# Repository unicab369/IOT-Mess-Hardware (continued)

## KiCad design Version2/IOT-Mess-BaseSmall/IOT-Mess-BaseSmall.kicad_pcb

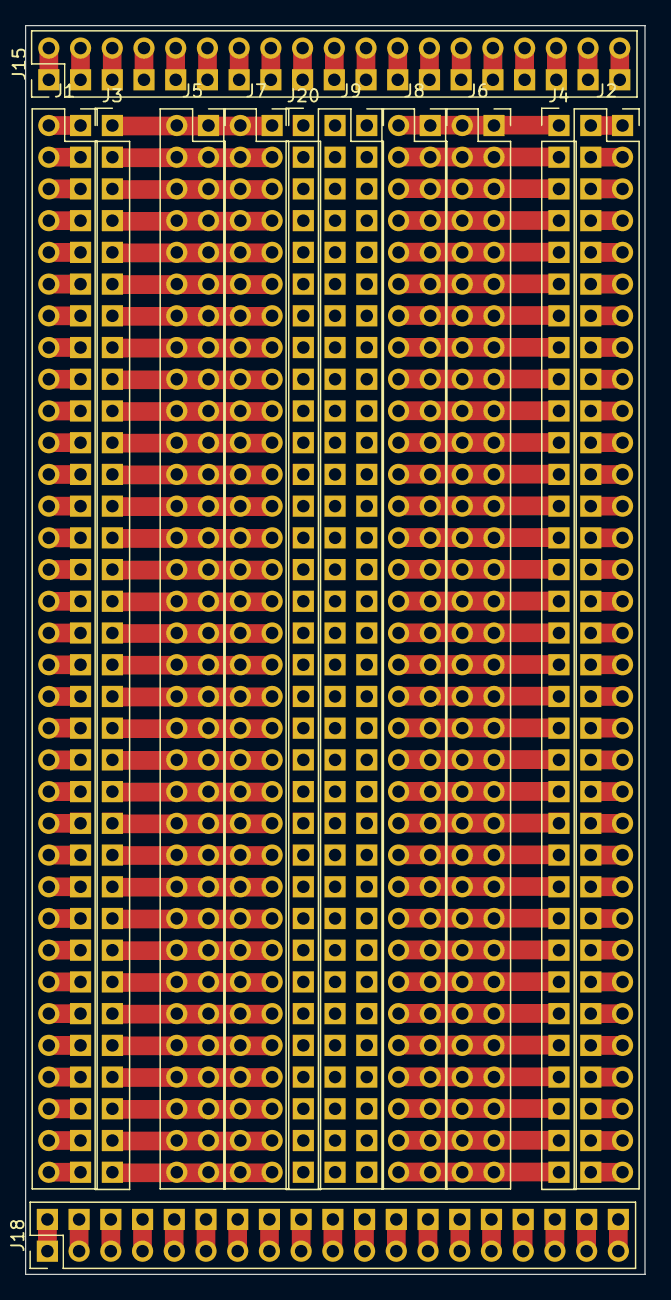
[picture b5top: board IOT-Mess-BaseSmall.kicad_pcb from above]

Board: 2 copper layers, 49.6 x 100.0 mm, 12 parts (0 on the bottom side), 174 nets.

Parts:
J1, J2, J5, J6, J7, J8, J9: Conn_02x34_Odd_Even; PinSocket_2x34_P2.54mm_Vertical
J3, J4, J20: Conn_01x34_Pin; PinHeader_1x34_P2.54mm_Vertical
J15, J18: Conn_02x19_Odd_Even; PinHeader_2x19_P2.54mm_Vertical

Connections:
/A1: J1.1, J1.2
/A2: J1.3, J1.4
/A3: J1.5, J1.6
/A4: J1.7, J1.8
/A5: J1.9, J1.10
/A6: J1.11, J1.12
/A7: J1.13, J1.14
/A8: J1.15, J1.16
/A9: J1.17, J1.18
/A10: J1.19, J1.20
/A11: J1.21, J1.22
/A12: J1.23, J1.24
/A13: J1.25, J1.26
/A14: J1.27, J1.28
/A15: J1.29, J1.30
/A16: J1.31, J1.32
/A17: J1.33, J1.34
/A18: J1.35, J1.36
/A19: J1.37, J1.38
/A20: J1.39, J1.40
/A21: J1.41, J1.42
/A22: J1.43, J1.44
/A23: J1.45, J1.46
/A24: J1.47, J1.48
/A25: J1.49, J1.50
/A26: J1.51, J1.52
/A27: J1.53, J1.54
/A28: J1.55, J1.56
/A29: J1.57, J1.58
/A30: J1.59, J1.60
/A31: J1.61, J1.62
/A32: J1.63, J1.64
/A33: J1.65, J1.66
/A34: J1.67, J1.68
/B1: J3.1, J5.1, J5.2, J7.1, J7.2
/B2: J3.2, J5.3, J5.4, J7.3, J7.4
/B3: J3.3, J5.5, J5.6, J7.5, J7.6
/B4: J3.4, J5.7, J5.8, J7.7, J7.8
/B5: J3.5, J5.9, J5.10, J7.9, J7.10
/B6: J3.6, J5.11, J5.12, J7.11, J7.12
/B7: J3.7, J5.13, J5.14, J7.13, J7.14
/B8: J3.8, J5.15, J5.16, J7.15, J7.16
/B9: J3.9, J5.17, J5.18, J7.17, J7.18
/B10: J3.10, J5.19, J5.20, J7.19, J7.20
/B11: J3.11, J5.21, J5.22, J7.21, J7.22
/B12: J3.12, J5.23, J5.24, J7.23, J7.24
/B13: J3.13, J5.25, J5.26, J7.25, J7.26
/B14: J3.14, J5.27, J5.28, J7.27, J7.28
/B15: J3.15, J5.29, J5.30, J7.29, J7.30
/B16: J3.16, J5.31, J5.32, J7.31, J7.32
/B17: J3.17, J5.33, J5.34, J7.33, J7.34
/B18: J3.18, J5.35, J5.36, J7.35, J7.36
/B19: J3.19, J5.37, J5.38, J7.37, J7.38
/B20: J3.20, J5.39, J5.40, J7.39, J7.40
/B21: J3.21, J5.41, J5.42, J7.41, J7.42
/B22: J3.22, J5.43, J5.44, J7.43, J7.44
/B23: J3.23, J5.45, J5.46, J7.45, J7.46
/B24: J3.24, J5.47, J5.48, J7.47, J7.48
/B25: J3.25, J5.49, J5.50, J7.49, J7.50
/B26: J3.26, J5.51, J5.52, J7.51, J7.52
/B27: J3.27, J5.53, J5.54, J7.53, J7.54
/B28: J3.28, J5.55, J5.56, J7.55, J7.56
/B29: J3.29, J5.57, J5.58, J7.57, J7.58
/B30: J3.30, J5.59, J5.60, J7.59, J7.60
/B31: J3.31, J5.61, J5.62, J7.61, J7.62
/B32: J3.32, J5.63, J5.64, J7.63, J7.64
/B33: J3.33, J5.65, J5.66, J7.65, J7.66
/B34: J3.34, J5.67, J5.68, J7.67, J7.68
/C1: J2.1, J2.2
/C2: J2.3, J2.4
/C3: J2.5, J2.6
/C4: J2.7, J2.8
/C5: J2.9, J2.10
/C6: J2.11, J2.12
/C7: J2.13, J2.14
/C8: J2.15, J2.16
/C9: J2.17, J2.18
/C10: J2.19, J2.20
/C11: J2.21, J2.22
/C12: J2.23, J2.24
/C13: J2.25, J2.26
/C14: J2.27, J2.28
/C15: J2.29, J2.30
/C16: J2.31, J2.32
/C17: J2.33, J2.34
/C18: J2.35, J2.36
/C19: J2.37, J2.38
/C20: J2.39, J2.40
/C21: J2.41, J2.42
/C22: J2.43, J2.44
/C23: J2.45, J2.46
/C24: J2.47, J2.48
/C25: J2.49, J2.50
/C26: J2.51, J2.52
/C27: J2.53, J2.54
/C28: J2.55, J2.56
/C29: J2.57, J2.58
/C30: J2.59, J2.60
/C31: J2.61, J2.62
/C32: J2.63, J2.64
/C33: J2.65, J2.66
/C34: J2.67, J2.68
/D1: J4.1, J6.1, J6.2, J8.1, J8.2
/D2: J4.2, J6.3, J6.4, J8.3, J8.4
/D3: J4.3, J6.5, J6.6, J8.5, J8.6
/D4: J4.4, J6.7, J6.8, J8.7, J8.8
/D5: J4.5, J6.9, J6.10, J8.9, J8.10
/D6: J4.6, J6.11, J6.12, J8.11, J8.12
/D7: J4.7, J6.13, J6.14, J8.13, J8.14
/D8: J4.8, J6.15, J6.16, J8.15, J8.16
/D9: J4.9, J6.17, J6.18, J8.17, J8.18
/D10: J4.10, J6.19, J6.20, J8.19, J8.20
/D11: J4.11, J6.21, J6.22, J8.21, J8.22
/D12: J4.12, J6.23, J6.24, J8.23, J8.24
/D13: J4.13, J6.25, J6.26, J8.25, J8.26
/D14: J4.14, J6.27, J6.28, J8.27, J8.28
/D15: J4.15, J6.29, J6.30, J8.29, J8.30
/D16: J4.16, J6.31, J6.32, J8.31, J8.32
/D17: J4.17, J6.33, J6.34, J8.33, J8.34
/D18: J4.18, J6.35, J6.36, J8.35, J8.36
/D19: J4.19, J6.37, J6.38, J8.37, J8.38
/D20: J4.20, J6.39, J6.40, J8.39, J8.40
/D21: J4.21, J6.41, J6.42, J8.41, J8.42
/D22: J4.22, J6.43, J6.44, J8.43, J8.44
/D23: J4.23, J6.45, J6.46, J8.45, J8.46
/D24: J4.24, J6.47, J6.48, J8.47, J8.48
/D25: J4.25, J6.49, J6.50, J8.49, J8.50
/D26: J4.26, J6.51, J6.52, J8.51, J8.52
/D27: J4.27, J6.53, J6.54, J8.53, J8.54
/D28: J4.28, J6.55, J6.56, J8.55, J8.56
/D29: J4.29, J6.57, J6.58, J8.57, J8.58
/D30: J4.30, J6.59, J6.60, J8.59, J8.60
/D31: J4.31, J6.61, J6.62, J8.61, J8.62
/D32: J4.32, J6.63, J6.64, J8.63, J8.64
/D33: J4.33, J6.65, J6.66, J8.65, J8.66
/D34: J4.34, J6.67, J6.68, J8.67, J8.68
/E1: J15.1, J15.2
/E2: J15.3, J15.4
/E3: J15.5, J15.6
/E4: J15.7, J15.8
/E5: J15.9, J15.10
/E6: J15.11, J15.12
/E7: J15.13, J15.14
/E8: J15.15, J15.16
/E9: J15.17, J15.18
/E10: J15.19, J15.20
/E11: J15.21, J15.22
/E12: J15.23, J15.24
/E13: J15.25, J15.26
/E14: J15.27, J15.28
/E15: J15.29, J15.30
/E16: J15.31, J15.32
/E17: J15.33, J15.34
/E18: J15.35, J15.36
/E19: J15.37, J15.38
/F1: J18.1, J18.2
/F2: J18.3, J18.4
/F3: J18.5, J18.6
/F4: J18.7, J18.8
/F5: J18.9, J18.10
/F6: J18.11, J18.12
/F7: J18.13, J18.14
/F8: J18.15, J18.16
/F9: J18.17, J18.18
/F10: J18.19, J18.20
/F11: J18.21, J18.22
/F12: J18.23, J18.24
/F13: J18.25, J18.26
/F14: J18.27, J18.28
/F15: J18.29, J18.30
/F16: J18.31, J18.32
/F17: J18.33, J18.34
/F18: J18.35, J18.36
/F19: J18.37, J18.38

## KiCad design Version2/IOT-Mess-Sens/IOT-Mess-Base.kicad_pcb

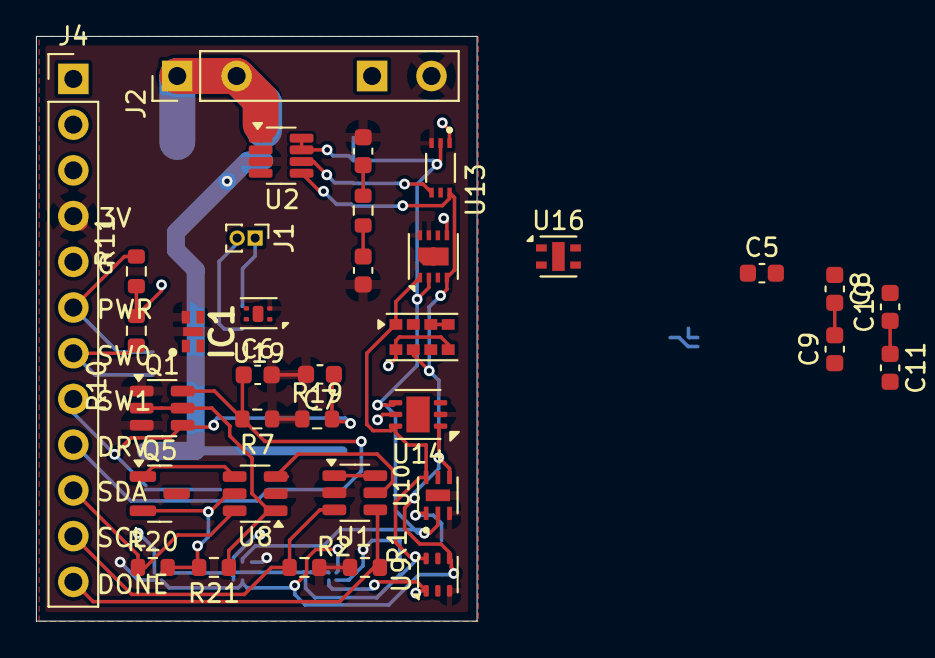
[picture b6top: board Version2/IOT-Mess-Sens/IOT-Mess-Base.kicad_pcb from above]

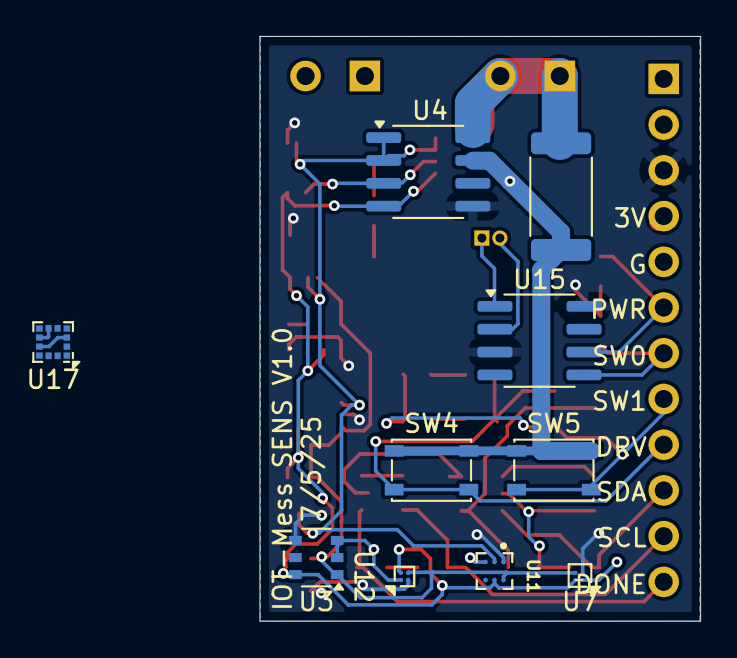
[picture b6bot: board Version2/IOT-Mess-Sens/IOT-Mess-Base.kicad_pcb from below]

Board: 2 copper layers, 24.5 x 32.5 mm, 45 parts (10 on the bottom side), 21 nets.

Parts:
C3, C6, C7: 0.1u; C_0603_1608Metric
C4: 1u; C_0603_1608Metric
C5: 2.2uF; C_0603_1608Metric
C8: .22u; C_0603_1608Metric
C9: 10u; C_0603_1608Metric
C10, C11: .1u; C_0603_1608Metric
IC1: SHT40I-AD1F-R2; SON80P150X150X59-5N
J1: Conn_01x02_Pin; PinHeader_1x02_P1.00mm_Vertical
J2: TP_4056; TP_Charger
J4: Conn_01x12_Pin; PinHeader_1x12_P2.54mm_Vertical
Q1: NM8205 PFETs; SOT-23-6
Q5: AO3401A; SOT-23
R1, R2, R7, R19, R20, R21: R; R_0603_1608Metric
R4: 0.1R; R_2512_6332Metric
R9: 5K; R_0603_1608Metric
R10, R11: 10K; R_0603_1608Metric
SW4, SW5: SW_Push; SW_SPST_PTS810
U1: TPL5110; SOT-23-6
U2: INA219AxDCN; SOT-23-8
U3: TLV493D; TSOP-6_1.65x3.05mm_P0.95mm
U4: INA219AxD; SOIC-8_3.9x4.9mm_P1.27mm
U5: SHT31-DIS; Sensirion_DFN-8-1EP_2.5x2.5mm_P0.5mm_EP1.1x1.7mm
U6: APDS-9960; Avago_APDS-9960
U7: QMC6309/WLCSP-4; WLCSP-4_0.8x0.8mm_Layout2x2_P0.4mm
U8: AND_Gate; SOT-23-6
U9: LTR-303ALS-01; Lite-On_LTR-303ALS-01
U10: OPT3001DNPR; SON65P200X200X65-7N
U11: HDC2010/DSBGA-6; BGA6C100X50P2X3_HDC2010YPAR
U12: MMC5633NJL/WLP-4; WLP-4_0.86x0.86mm_P0.4mm
U13: BH1750FVI-TR; XDCR_BH1750FVI-TR
U14: T117W; TDFN-6-1EP_2.5x2.5mm_P0.65mm_EP1.3x2mm
U15: DS1307Z+; SOIC-8_3.9x4.9mm_P1.27mm
U16: ENS210; AMS_QFN-4-1EP_2x2mm_P0.95mm_EP0.7x1.6mm
U17: LIS2MDL; LGA-12_2x2mm_P0.5mm
U19: MTS4; DFN-4L

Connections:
+3.3V: C4.1, C5.1, C9.1, C10.1, C11.1, IC1.3 (VDD), J4.3, R9.1, R10.2, R11.1, U2.4 (VS), U3.4 (VDD), U4.5 (VS), U5.5 (VDD), U6.5 (LED_A), U6.8 (VCC), U7.B1 (VDD), U9.1 (VDD), U10.1 (VDD), U11.A1 (VDD), U12.B1 (VDD), U13.1 (VCC), U14.5 (VDD), U15.3 (VBAT), U15.8 (VCC), U16.1 (VDD), U17.3 (~CS), U17.9 (Vdd), U19.3 (VDD)
ADDR: U2.7 (A0), U2.8 (A1), U4.1 (A1), U4.2 (A0), U5.2 (ADDR), U10.2 (ADDR), U11.B1 (ADDR), U13.2 (ADDR), U14.4 (ADDR)
DONE: J4.12, R1.2, U1.4 (DONE)
EN: J4.10, R20.1, U8.6 (C)
GND: C3.2, C4.2, C5.2, C6.2, C7.2, C8.2, C9.2, C10.2, IC1.4 (VSS), IC1.5 (EP), J2.4, J4.4, Q1.1 (D1), Q1.3 (S2), R1.1, R2.1, R7.1, R19.1, U1.2 (GND), U2.3 (GND), U3.2 (GND), U3.3 (GND), U4.6 (GND), U5.7 (R), U5.8 (VSS), U5.9 (VSS), U6.6 (GND), U7.A1 (GND), U8.2 (GND), U9.3 (GND), U10.3 (GND), U10.7 (EXP), U11.C1 (GND), U12.A1 (VSA), U13.3 (GND), U14.2 (GND), U15.4 (GND), U16.4 (GND), U16.5 (GND), U17.6 (GND), U17.8 (GND), U19.2 (GND)
LSW0: C6.1, J4.9, Q1.6 (G1), R7.2, SW4.2
LSW1: C7.1, J4.8, Q1.4 (G2), R19.2, SW5.2
unnamed: J1.1, U15.1 (X1)
unnamed: J1.2, U15.2 (X2)
unnamed: Q5.1 (G), U8.4 (Y)
unnamed: U1.5 (DRV), U8.3 (B)
unnamed: U6.3 (LDR), U6.4 (LED_K)
unnamed: Q1.2 (S1/D2), Q1.5 (S1/D2), R21.1, U8.1 (A)
unnamed: C3.1, R9.2, U13.5 (DVI)
unnamed: C8.1, U17.5 (C1)
unnamed: C11.2, U17.10 (Vdd_IO)
R_DELAY: J4.11, R2.2, U1.3 (DELAY/M_DRV)
SCL_0: IC1.2 (SCL), J4.6, R11.2, U2.5 (SCL), U3.6 (SDA/ADDR), U4.4 (SCL), U5.4 (SCL), U6.7 (SCL), U7.A2 (SCL), U9.4 (SCL), U10.4 (SCL), U11.B2 (SCL), U12.A2 (SCL), U13.6 (SCL), U14.1 (SCL), U15.6 (SCL), U16.2 (SCL), U17.4 (SDA/SDI/SDO), U19.1 (SCL)
SDA_0: IC1.1 (SDA), J4.7, R10.1, U2.6 (SDA), U3.1 (SCL/INT), U4.3 (SDA), U5.1 (SDA), U6.1 (SDA), U7.B2 (SDA), U9.6 (SDA), U10.6 (SDA), U11.A2 (SDA), U12.B2 (SDA), U13.4 (SDA), U14.6 (SDA), U15.5 (SDA), U16.3 (SDA), U17.1 (SCL/SPC), U19.4 (SDA)
Va: J2.1, J2.2, R4.2, U2.1 (IN+), U4.8 (IN+)
Vb: Q5.2 (S), R4.1, R20.2, R21.2, SW4.1, SW5.1, U1.1 (VDD), U1.6 (EN/ONE_SHOT), U2.2 (IN-), U4.7 (IN-), U8.5 (Vcc)
